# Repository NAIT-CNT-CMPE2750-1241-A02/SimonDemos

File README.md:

# SimonDemos
Demos used in this course, including the sample project.

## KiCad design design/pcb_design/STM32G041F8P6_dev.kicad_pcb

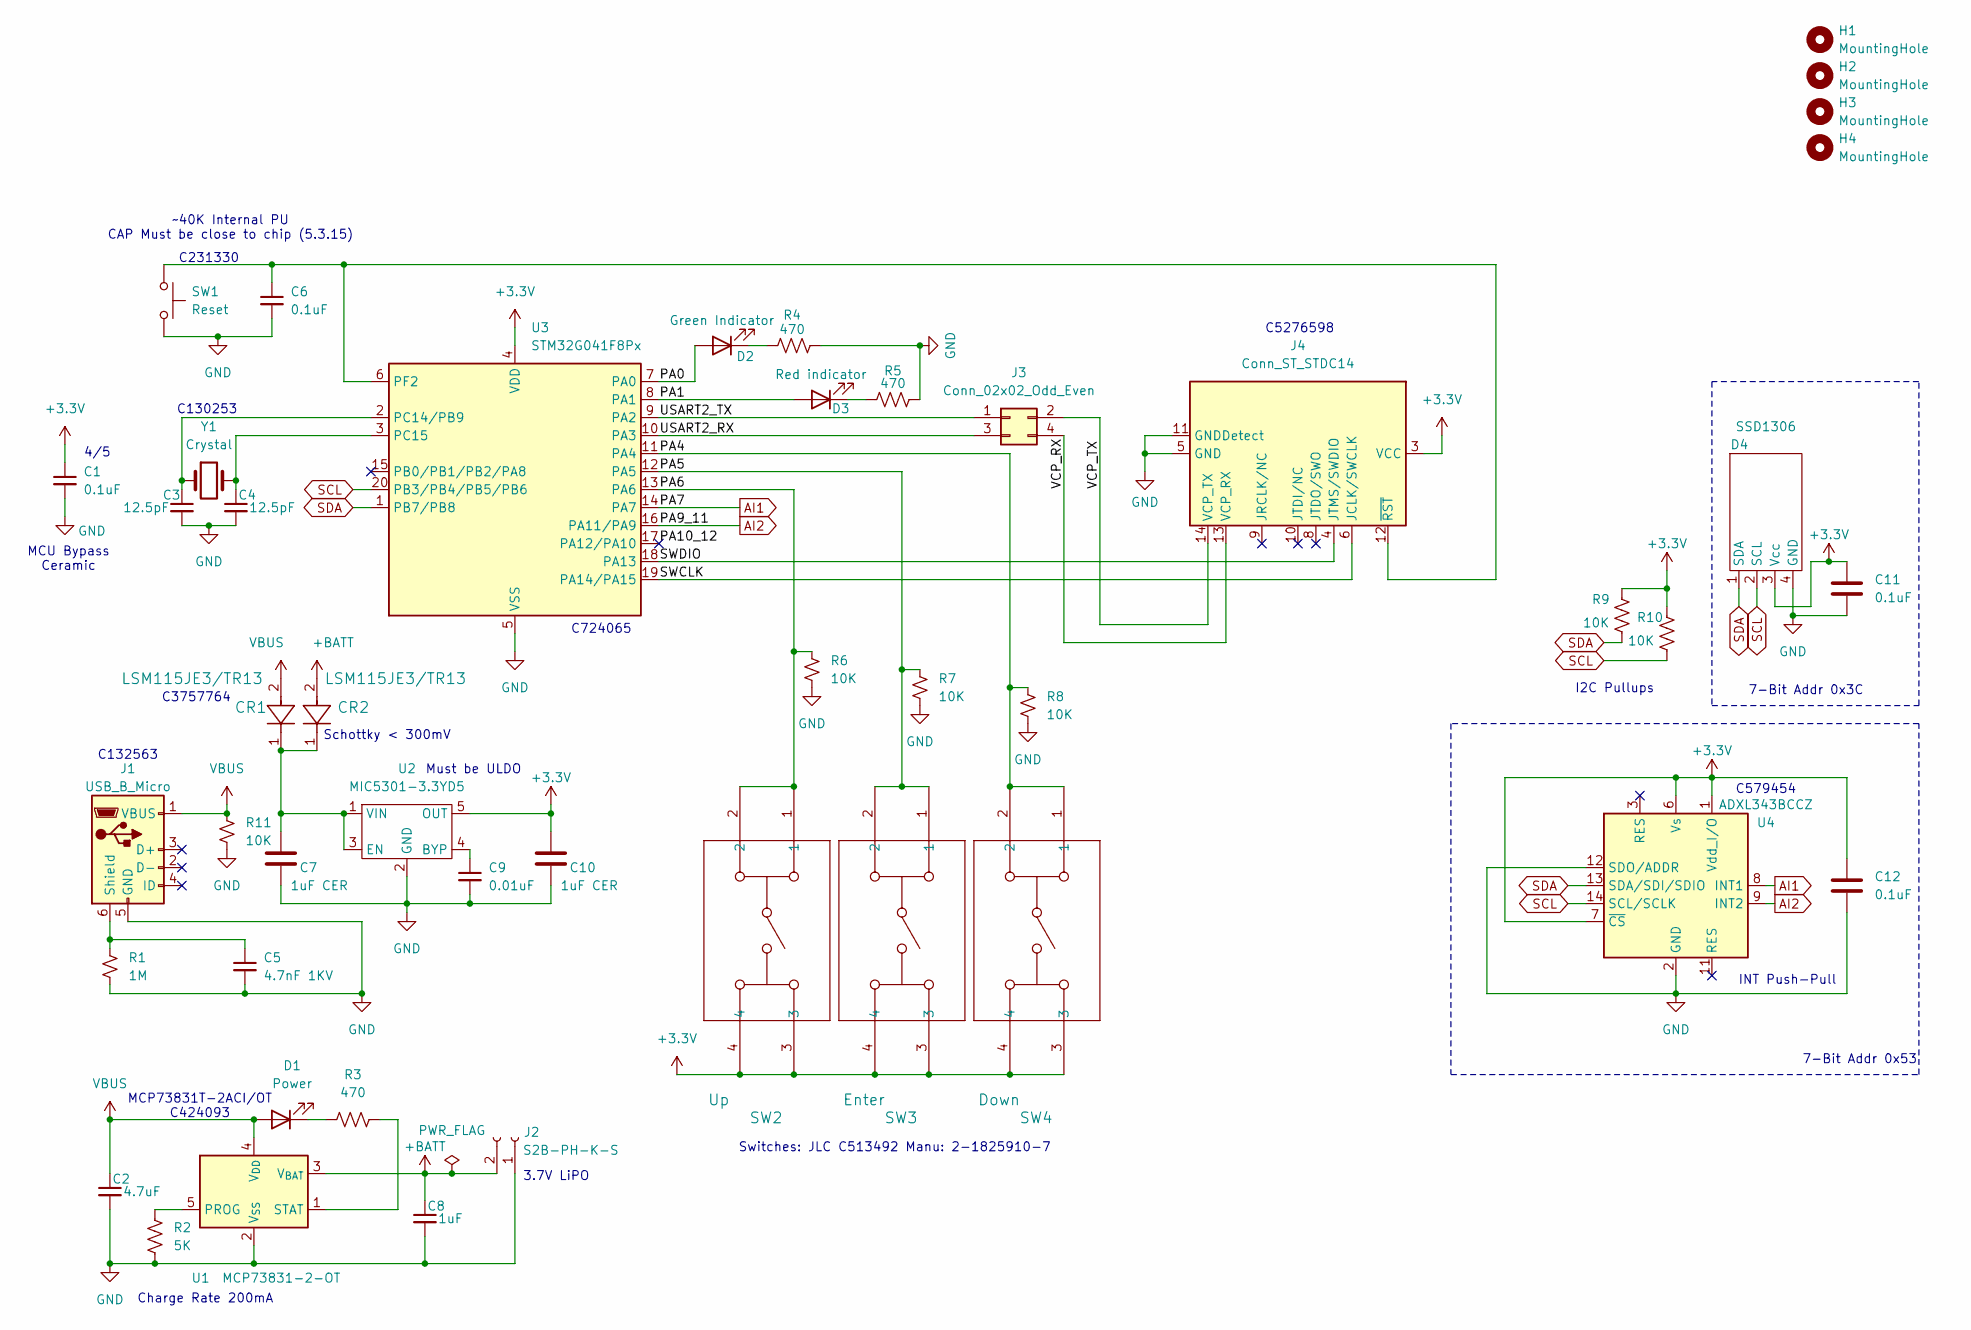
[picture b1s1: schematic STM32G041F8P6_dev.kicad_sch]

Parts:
C1, C6, C11, C12: 0.1uF; C_0603_1608Metric
C2: 4.7uF; C_1206_3216Metric
C3, C4: 12.5pF; C_0603_1608Metric
C5: 4.7nF 1KV; C_0805_2012Metric
C7, C10: 1uF CER; C_1206_3216Metric
C8: 1uF; C_1206_3216Metric
C9: 0.01uF; C_0805_2012Metric
CR1, CR2: LSM115JE3/TR13; DO-214BA_MCH
D1: Power; LED_0805_2012Metric
D2: Green Indicator; LED_0805_2012Metric
D3: Red indicator; LED_0805_2012Metric
D4: SSD1306; SmallOLED
H1, H2, H3, H4: MountingHole; MountingHole_3.2mm_M3
J1: USB_B_Micro; USB_Micro-B_Amphenol_10118194_Horizontal
J2: S2B-PH-K-S; JST_PH_S2B-PH-K_1x02_P2.00mm_Horizontal
J3: Conn_02x02_Odd_Even; PinHeader_2x02_P2.54mm_Vertical
J4: Conn_ST_STDC14; PinHeader_2x07_P1.27mm_Vertical_SMD
R1: 1M; R_0805_2012Metric
R2: 5K; R_0805_2012Metric
R3, R4, R5: 470; R_0805_2012Metric
R6, R7, R8, R9, R10, R11: 10K; R_0805_2012Metric
SW1: Reset; SW_SPST_B3U-1000P
SW2: Up; SW4_1825910-G_TEC
SW3: Enter; SW4_1825910-G_TEC
SW4: Down; SW4_1825910-G_TEC
U1: MCP73831-2-OT; SOT-23-5
U2: MIC5301-3.3YD5; TSOT-23-5
U3: STM32G041F8Px; TSSOP-20_4.4x6.5mm_P0.65mm
U4: ADXL343BCCZ; LGA-14_3x5mm_P0.8mm_LayoutBorder1x6y
Y1: Crystal; Crystal_SMD_3215-2Pin_3.2x1.5mm

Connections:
+3.3V: C1.1, C10.2, C11.1, C12.1, D4.3 (Vcc), J4.3 (VCC), R9.2, R10.2, SW2.3, SW2.4, SW3.3, SW3.4, SW4.3, SW4.4, U2.5 (OUT), U3.4 (VDD), U4.1 (Vdd_I/O), U4.6 (Vs), U4.7 (~CS)
+BATT: C8.1, CR2.2, J2.2, U1.3 (V_{BAT})
/PA0: D2.2 (A), U3.7 (PA0)
/PA1: D3.2 (A), U3.8 (PA1)
/PA4: R8.2, SW4.1, SW4.2, U3.11 (PA4)
/PA5: R7.2, SW3.1, SW3.2, U3.12 (PA5)
/PA6: R6.2, SW2.1, SW2.2, U3.13 (PA6)
/PA10_12: U3.17 (PA12/PA10)
/SWCLK: J4.6 (JCLK/SWCLK), U3.19 (PA14/PA15)
/SWDIO: J4.4 (JTMS/SWDIO), U3.18 (PA13)
/USART2_RX: J3.3, U3.10 (PA3)
/USART2_TX: J3.1, U3.9 (PA2)
/VCP_RX: J3.4, J4.13 (VCP_RX)
/VCP_TX: J3.2, J4.14 (VCP_TX)
AI1: U3.14 (PA7), U4.8 (INT1)
AI2: U3.16 (PA11/PA9), U4.9 (INT2)
GND: C1.2, C2.2, C3.2, C4.2, C5.2, C6.2, C7.1, C8.2, C9.2, C10.1, C11.2, C12.2, D4.4 (GND), J1.5 (GND), J2.1, J4.5 (GND), J4.7 (GND), J4.11 (GNDDetect), R1.2, R2.2, R4.1, R5.1, R6.1, R7.1, R8.1, R11.1, SW1.2, U1.2 (V_{SS}), U2.2 (GND), U3.5 (VSS), U4.2 (GND), U4.4 (GND), U4.5 (GND), U4.12 (SDO/ADDR)
unnamed: D1.1 (K), R3.2
unnamed: D2.1 (K), R4.2
unnamed: D3.1 (K), R5.2
unnamed: C5.1, J1.6 (Shield), R1.1
unnamed: C6.1, J4.12 (~RST), SW1.1, U3.6 (PF2)
unnamed: R2.1, U1.5 (PROG)
unnamed: R3.1, U1.1 (STAT)
unnamed: C9.1, U2.4 (BYP)
unnamed: C7.2, CR1.1, CR2.1, U2.1 (VIN), U2.3 (EN)
unnamed: C3.1, U3.2 (PC14/PB9), Y1.1
unnamed: C4.1, U3.3 (PC15), Y1.2
SCL: D4.2 (SCL), R10.1, U3.20 (PB3/PB4/PB5/PB6), U4.14 (SCL/SCLK)
SDA: D4.1 (SDA), R9.1, U3.1 (PB7/PB8), U4.13 (SDA/SDI/SDIO)
VBUS: C2.1, CR1.2, D1.2 (A), J1.1 (VBUS), R11.2, U1.4 (V_{DD})

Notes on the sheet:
4/5
~40K Internal PU CAP Must be close to chip (5.3.15)
MCU Bypass Ceramic
3.7V LiPO
Charge Rate 200mA
I2C Pullups
Switches: JLC C513492 Manu: 2-1825910-7
C3757764
C5276598
C130253
C579454
MCP73831T-2ACI/OT C424093
INT Push-Pull
C724065
7-Bit Addr 0x3C
C132563
Must be ULDO
C231330
Schottky < 300mV
7-Bit Addr 0x53

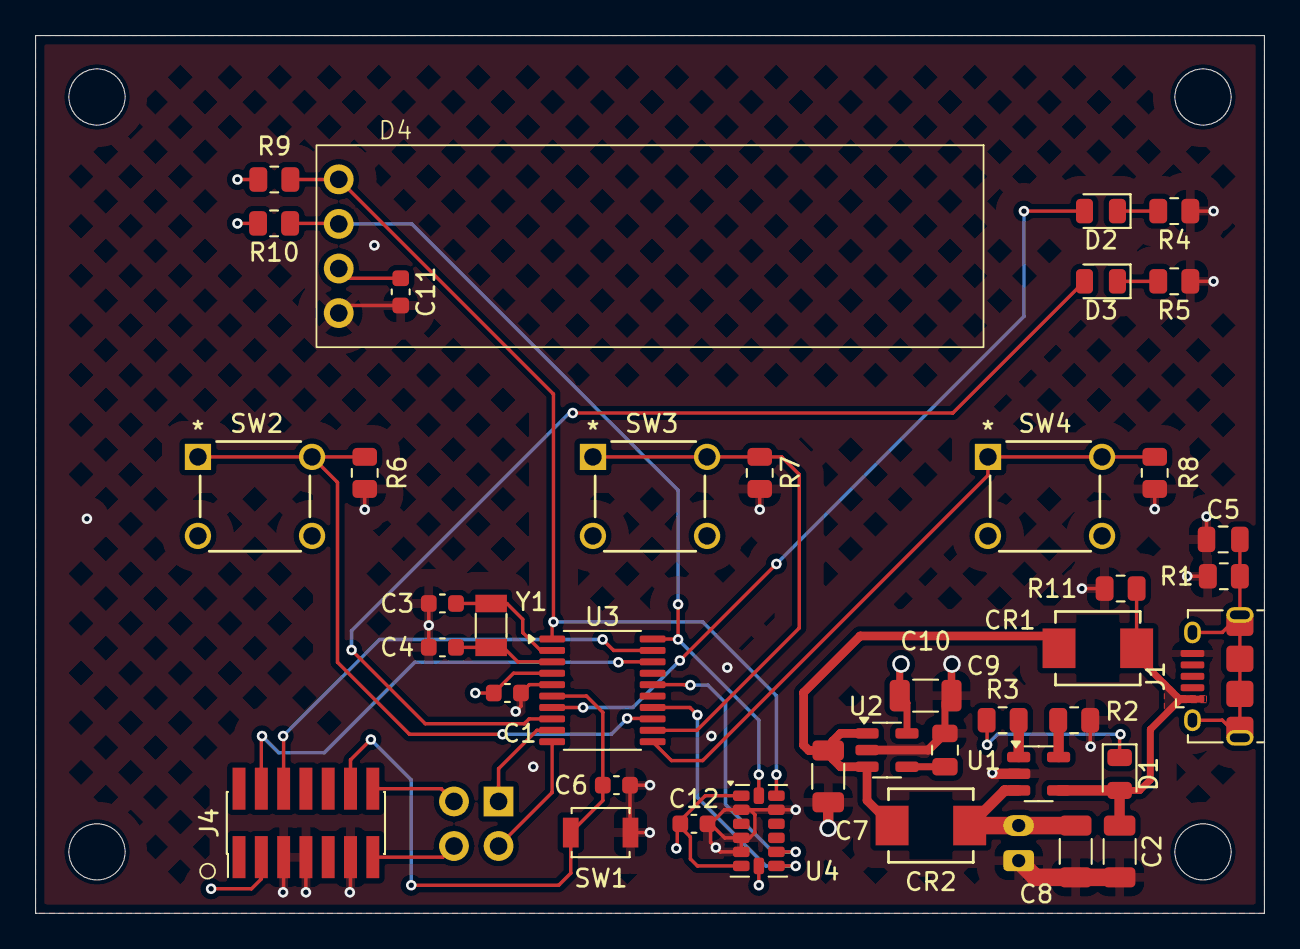
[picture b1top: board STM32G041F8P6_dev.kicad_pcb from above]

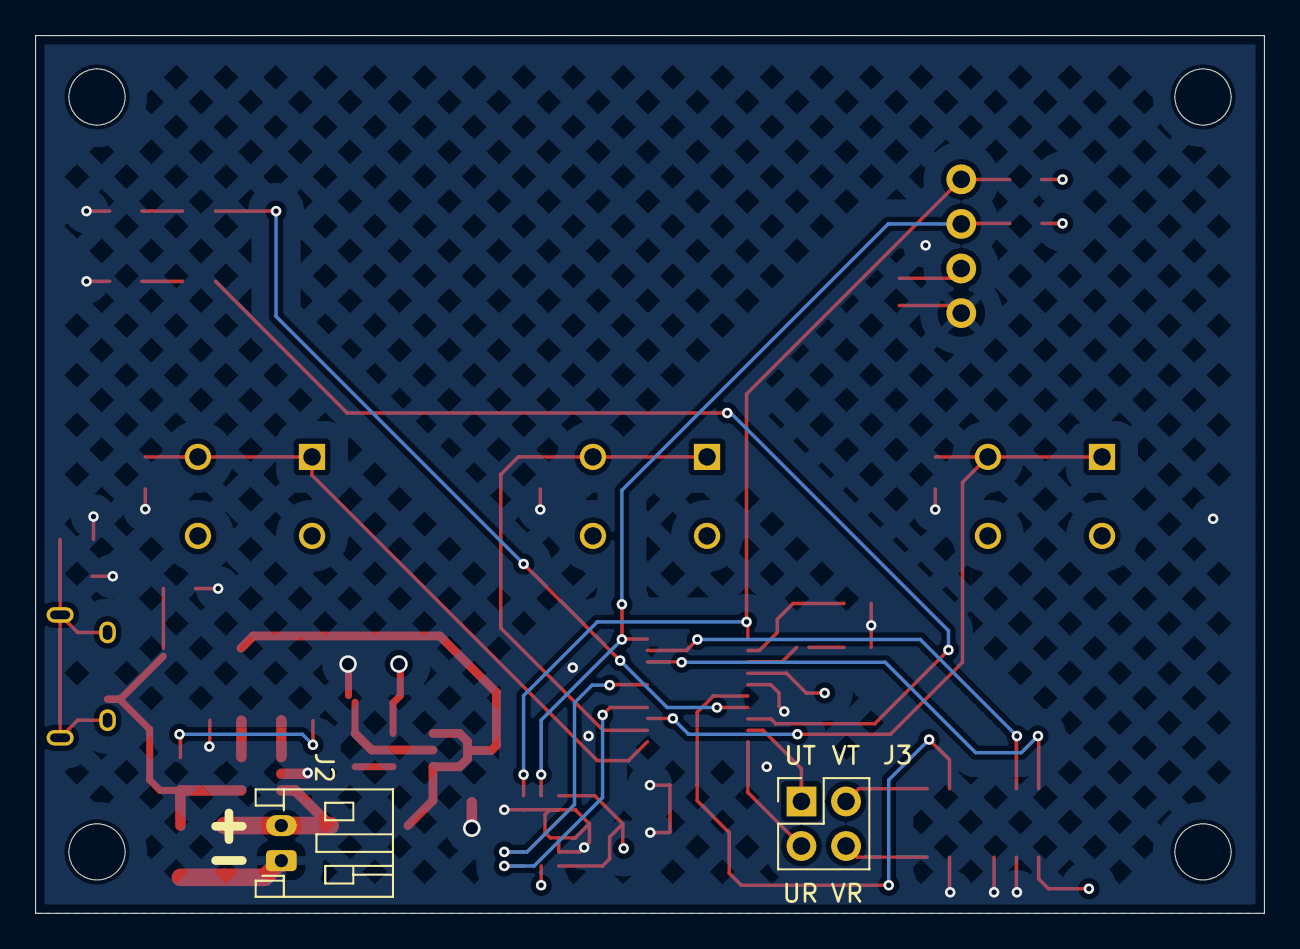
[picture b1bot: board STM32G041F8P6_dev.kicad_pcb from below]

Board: 4 copper layers, 70.0 x 50.0 mm, 46 parts (2 on the bottom side), 30 nets.

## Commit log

2024-09-10 added some minor research stuff, charger datasheet
2024-09-13 added mote detail to project
2024-09-24 updates to breadboard demo
2024-10-16 added interrupt line to micro from SSSR1.8
2024-10-18 mods
2024-10-24 updates!
2024-10-24 updates to pcb
2024-10-24 pcb updates, initial layout
2024-10-24 pcb updates
2024-10-31 PCB Design Updates
2024-11-06 Final changes before manufacture.
2025-09-24 added net labels
